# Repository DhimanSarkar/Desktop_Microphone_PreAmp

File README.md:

# Desktop Microphone Pre-Amplifier

## Dependencies
- [KiCAD](https://kicad.org)

## Licences
[CERN-OHL-S](https://ohwr.org/cern_ohl_s_v2.txt)
[GNU AGPLv3](https://www.gnu.org/licenses/gpl-3.0.txt)
[CC-BY-SA-4.0](https://creativecommons.org/licenses/by-sa/4.0/legalcode)

See '[LICENCE](/LICENCE)', '[LICENCE.CERN-OHL-S.txt](/LICENCE.CERN-OHL-S.txt)', '[LICENCE.GNU-AGPLv3.txt](/LICENCE.GNU-AGPLv3.txt)', '[LICENCE.CC-BY-SA-4.0.txt](/LICENCE.CC-BY-SA-4.0.txt)' for more details.

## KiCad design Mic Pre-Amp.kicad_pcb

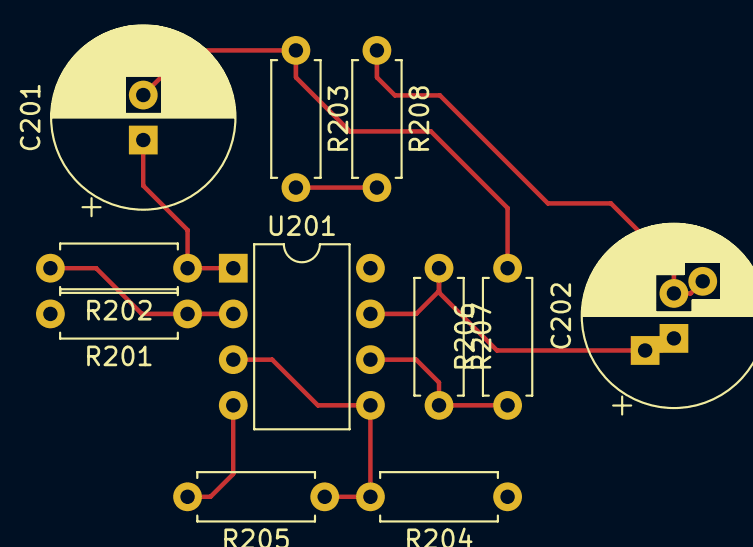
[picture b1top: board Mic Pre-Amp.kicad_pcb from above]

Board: 2 copper layers, 11 parts (0 on the bottom side), 9 nets.

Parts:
C201: 220u; CP_Radial_D10.0mm_P2.50mm
C202: 220u; CP_Radial_D10.0mm_P2.50mm_P5.00mm
R201, R206, R207: 1k; R_Axial_DIN0207_L6.3mm_D2.5mm_P7.62mm_Horizontal
R202, R203: R; R_Axial_DIN0207_L6.3mm_D2.5mm_P7.62mm_Horizontal
R204, R205: 100k; R_Axial_DIN0207_L6.3mm_D2.5mm_P7.62mm_Horizontal
R208: 10k; R_Axial_DIN0207_L6.3mm_D2.5mm_P7.62mm_Horizontal
U201: TL072; DIP-8_W7.62mm

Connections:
+5V: R204.1, U201.8
Amplified_Output_to_PC_2: C202.2, R208.1
GND: R203.2, R205.2, R208.2, U201.4
GNDREF: R204.2, R205.1, U201.3, U201.5
unnamed: C201.1, R202.1, U201.1
unnamed: C201.2, R203.1, R206.2
unnamed: C202.1, R207.1, U201.7
unnamed: R201.1, R202.2, U201.2
unnamed: R206.1, R207.2, U201.6

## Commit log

2021-05-23 INIT
2021-05-23 v1.1 | Working | have 5KHz and harmonics noise form PC USB power supply
2021-05-28 v2.1 | Op-Amp Based | Working | have 20KHz noice, Source of noise unknown, Clipping Happens at low frequencies (100Hz)
2021-09-27 v0.2b
